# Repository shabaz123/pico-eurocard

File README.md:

# pico-eurocard

This repository contains PCB Gerber files and bill of materials for a [Pi Pico Eurocard Development Board](https://community.element14.com/products/raspberry-pi/b/blog/posts/pi-pico-eurocard-development-board). See James' [Workshop Wednesday's Video](https://community.element14.com/challenges-projects/element14-presents/workbenchwednesdays/w/documents/28083/workbench-wednesdays-70-why-you-need-a-raspberry-pi-pico-development-board-by-shabaz) which demonstrates the revision 2.0 board.

Right-click below to open in new window to watch the video for a quick explanation!

The current revision 2.2 board has a few slight impromements to make it easier to solder, and has enlarged text silkscreen as can be seen in the image below.

Latest [Schematic](https://github.com/shabaz123/pico-eurocard/blob/main/pico-euro-kicad-source/pico-euro-schematic.pdf) and [Bill of Materials](https://github.com/shabaz123/pico-eurocard/blob/main/pico-euro-kicad-source/pico-euro-rev-2-2-bill-of-materials.pdf) and [Zip file of Gerbers](https://github.com/shabaz123/pico-eurocard/blob/main/export_pico_euro_rev_2_2.zip), (click on the Download button on the right) ready for sending to any PCB factory.

License: The pico-eurocard project is distributed under the CC BY-NC-SA 4.0 license. Please share any changes you make, so that others can contribute and benefit from them.

Board Revision History

Rev 1 - Resistors R2 and R3 are mistakenly connected to GND. They should be connected to 3V3. See the rev1-i2c-fix.png file to see the fix (requires two traces to be cut, and a wire to be soldered).

Rev 1.1 - Fixes the R2 and R3 issue that Rev 1 had. Also adds connections for an SPI TFT display, and exposes I2C, GND and VSYS onto some additional pins on the edge connector for some more flexibility. Also, the 7805 regulator has a bit more space, to allow heatsinks to more easily fit.

Rev 1.2 - Adds some pads on the underside of the SOIC footprints, that are suitable for decoupling capacitors, and for optional output feedback components if the soldered SOIC component is an op-amp. Also, the corners of the board have been rounded very slightly (0.5 mm radius). Previously, the corners had no radius.

Rev 1.3 - Added some pads to make it slightly easier to plug on a daughter board made from (say) stripboard.

Rev 2.0 - Removed SPI TFT pins, since there was some incompatibility with recently available displays. Added micro SD card socket.

Rev 2.2 - Very similar to 2.0 version, but with far more legible silkscreen, and with all surface-mount components (including the micro SD socket) on one side of the board, for easier production. Also added a resistor for more gate protection with partially assembled boards.

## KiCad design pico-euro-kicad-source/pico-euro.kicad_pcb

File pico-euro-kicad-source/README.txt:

Please see the following links for more information on this project, and to comment on it:

https://community.element14.com/products/raspberry-pi/b/blog/posts/pi-pico-eurocard-development-board

https://community.element14.com/challenges-projects/element14-presents/workbenchwednesdays/w/documents/28083/workbench-wednesdays-70-why-you-need-a-raspberry-pi-pico-development-board-by-shabaz?ICID=workbenchwed-episode-list

https://community.element14.com/tags/pico_5F00_eurocard

Software Links:
https://github.com/jancumps/picoprobe/releases

https://github.com/shabaz123/rp2040tools

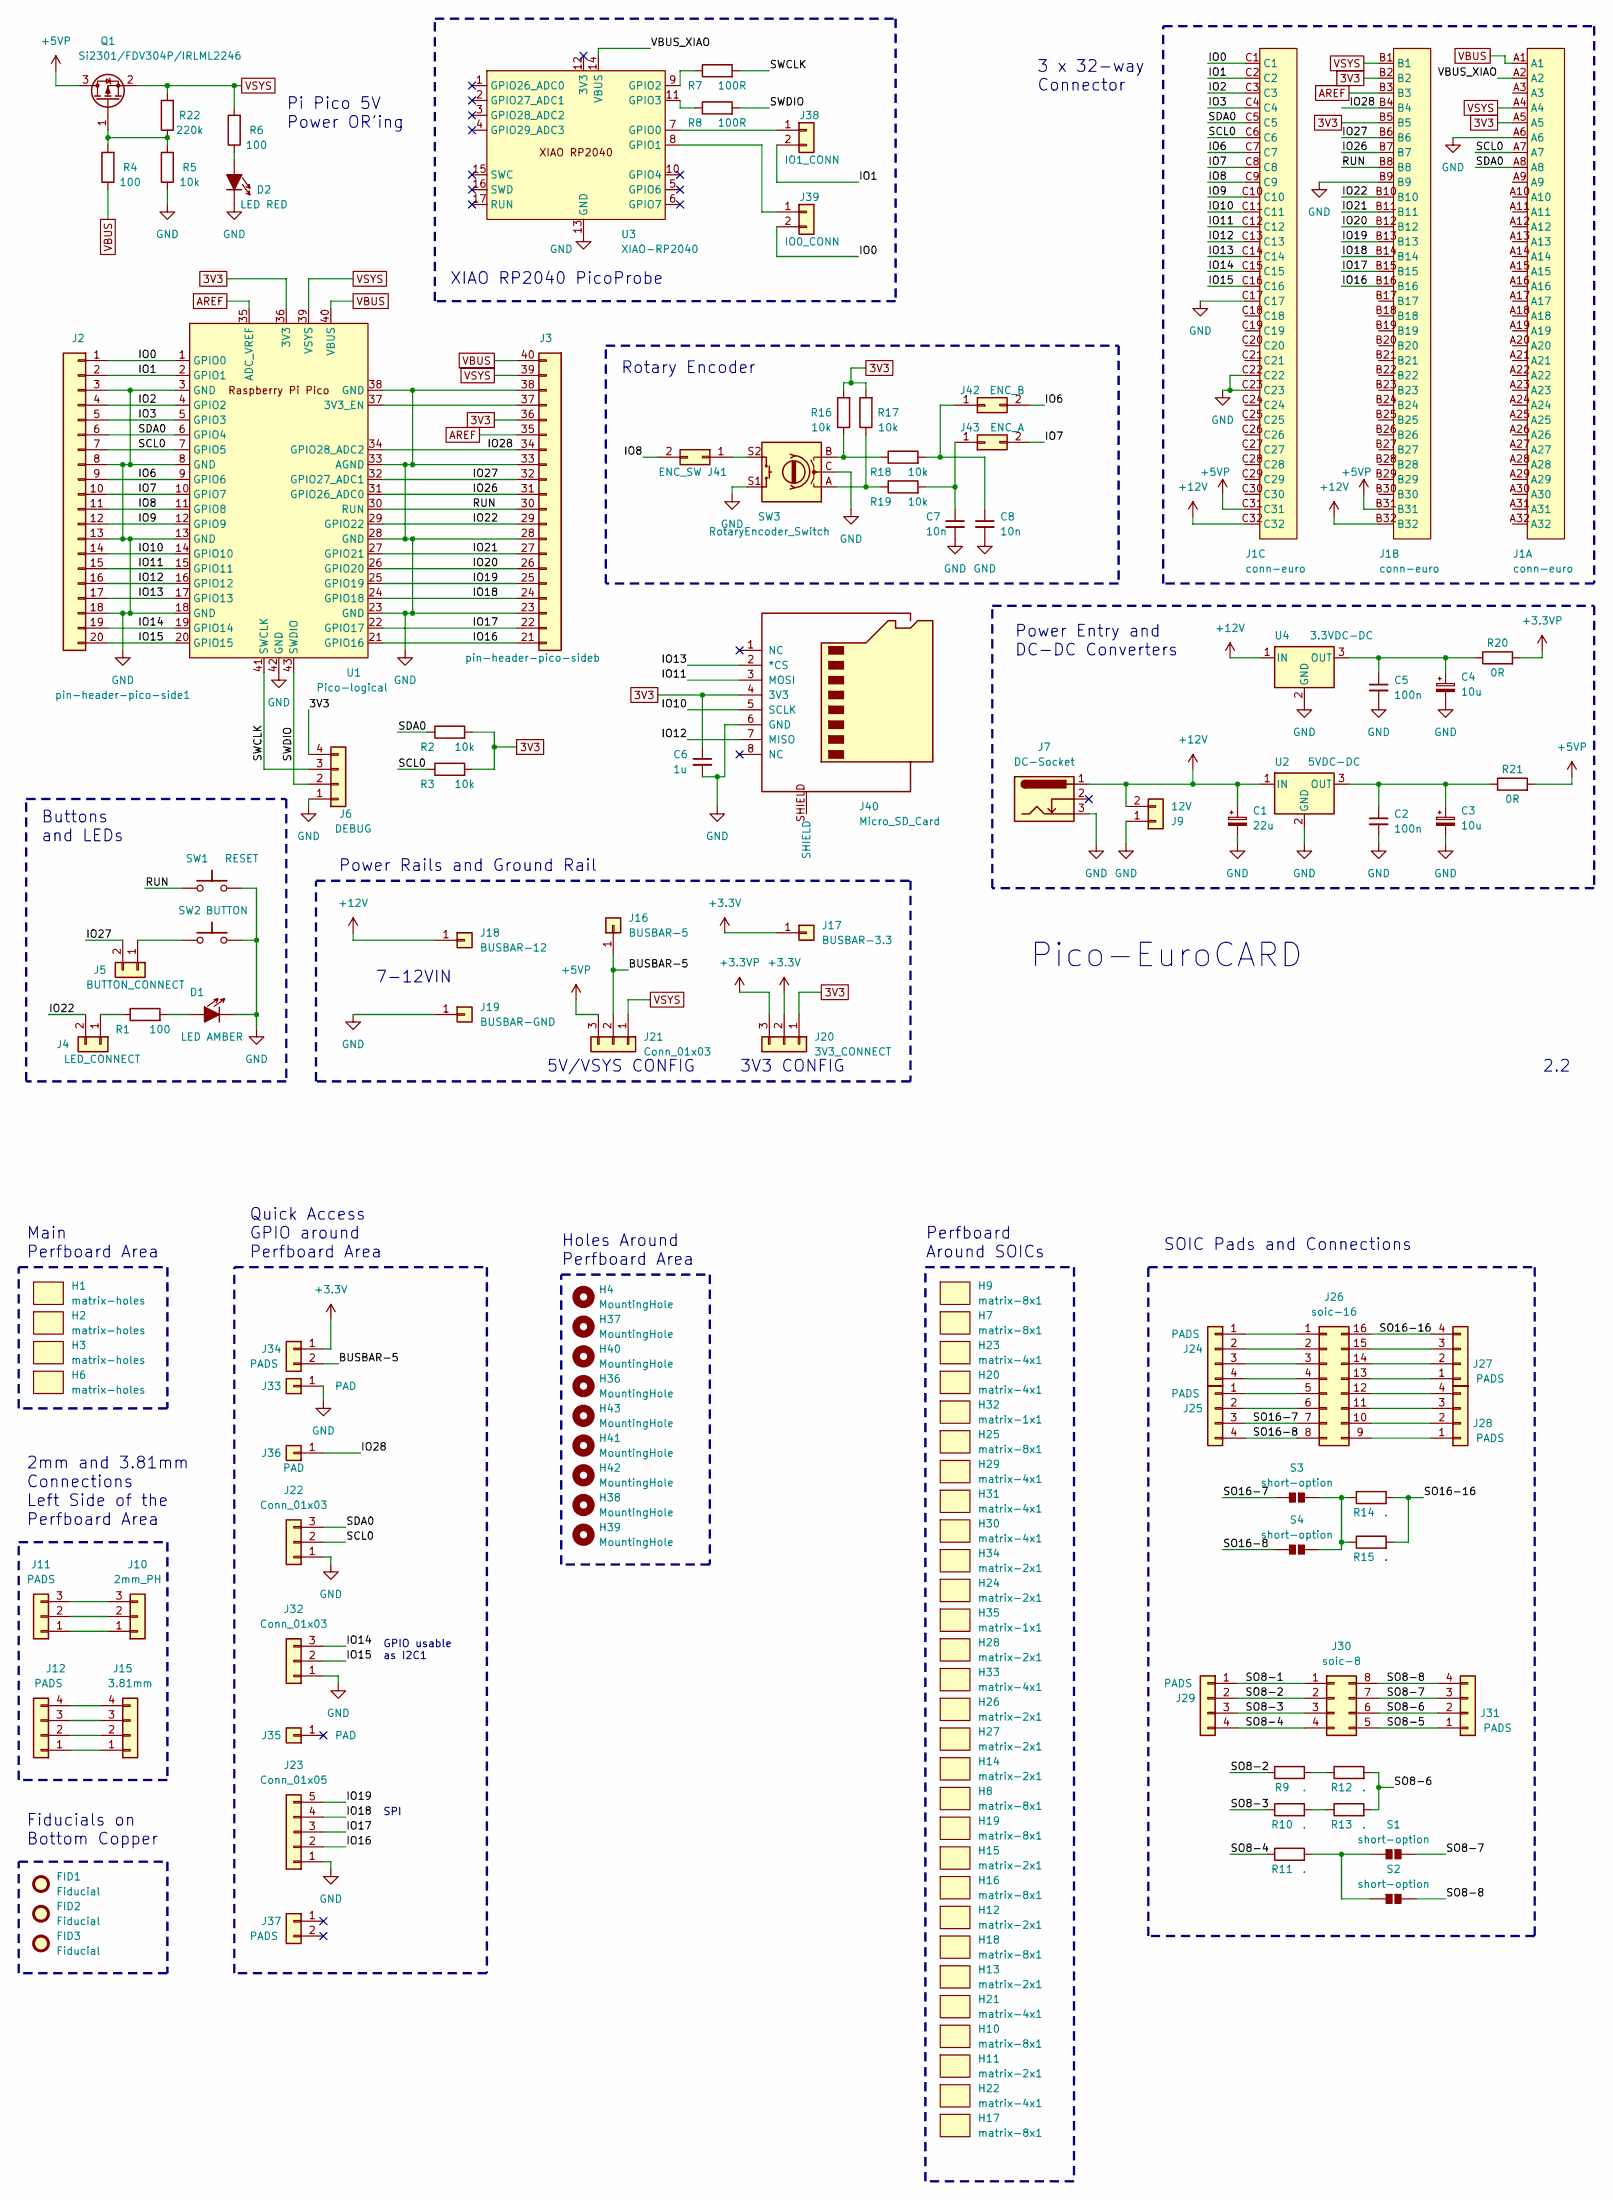
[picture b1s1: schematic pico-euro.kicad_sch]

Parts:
C1: 22u; CP_Radial_D6.3mm_P2.50mm
C2, C5: 100n; C_0805_2012Metric_Pad1.18x1.45mm_HandSolder
C3, C4: 10u; CP_Radial_D6.3mm_P2.50mm
C6: 1u; C_1210_3225Metric_Pad1.33x2.70mm_HandSolder
C7, C8: 10n; C_0805_2012Metric_Pad1.18x1.45mm_HandSolder
D1: LED AMBER; LED_D3.0mm
D2: LED RED; LED_D3.0mm
FID1, FID2, FID3: Fiducial; Fiducial_1mm_Mask2mm
H1, H2, H3, H6: matrix-holes; matrix-33-4
H4, H36, H37, H38, H39, H40, H41, H42, H43: MountingHole; HOLE_BARE_0.9mm
H7, H8, H9, H10, H16, H17, H18, H19, H25: matrix-8x1
H11, H12, H13, H14, H15, H24, H26, H27, H28, H34: matrix-2x1
H20, H21, H22, H23, H29, H30, H31, H33: matrix-4x1
H32, H35: matrix-1x1
J1: conn-euro; Eurocard-Plug-Type-C
J2: pin-header-pico-side1
J3: pin-header-pico-sideb; pin-header-pico-side2
J4: LED_CONNECT; PinHeader_1x02_P2.54mm_Vertical
J5: BUTTON_CONNECT; PinHeader_1x02_P2.54mm_Vertical
J6: DEBUG; PinHeader_1x04_P2.54mm_Vertical
J7: DC-Socket; DC-Jack-10
J9: 12V; TerminalBlock_Phoenix_PT-1,5-2-3.5-H_1x02_P3.50mm_Horizontal
J10: 2mm_PH; JST_PH_3_VERT
J11: PADS; pads3-euro
J12, J24, J25, J27, J28, J29, J31: PADS; pads4-euro
J15: 3.81mm; array-3.81
J16: BUSBAR-5; busbar-20div2
J17: BUSBAR-3.3; busbar-20
J18: BUSBAR-12; busbar-20div4
J19: BUSBAR-GND; busbar-20
J20: 3V3_CONNECT; PinHeader_1x03_P2.54mm_Vertical
J21: Conn_01x03; PinHeader_1x03_P2.54mm_Vertical
J22, J32: Conn_01x03; pads3-euro
J23: Conn_01x05; pads5-euro
J26: soic-16; SOIC-16-proto
J30: soic-8; SOIC-8-proto
J33, J35, J36: PAD; pads1-euro
J34, J37: PADS; pads2-euro
J38: IO1_CONN; PinHeader_1x02_P2.54mm_Vertical
J39: IO0_CONN; PinHeader_1x02_P2.54mm_Vertical
J40: Micro_SD_Card; microsd-generic
J41: ENC_SW; PinHeader_1x02_slim
J42: ENC_B; PinHeader_1x02_slim
J43: ENC_A; PinHeader_1x02_slim
Q1: Si2301/FDV304P/IRLML2246; SOT-23_Handsoldering
R1, R4, R6: 100; R_0805_2012Metric_Pad1.20x1.40mm_HandSolder
R2, R3, R5, R16, R17, R18, R19: 10k; R_0805_2012Metric_Pad1.20x1.40mm_HandSolder
R7, R8: 100R; R_0805_2012Metric_Pad1.20x1.40mm_HandSolder
R9, R10, R11, R12, R13, R14: .; R_0805_2012Metric_Pad1.20x1.40mm_HandSolder
R15: .; R_1210_3225Metric_Pad1.30x2.65mm_HandSolder
R20, R21: 0R; R_0805_2012Metric_Pad1.20x1.40mm_HandSolder
R22: 220k; R_0805_2012Metric_Pad1.20x1.40mm_HandSolder
S1, S2, S3, S4: short-option; short-option-small
SW1: RESET; SW_PUSH_6mm
SW2: BUTTON; SW_PUSH_6mm
SW3: RotaryEncoder_Switch; Encoder-and-Switch
U1: Pico-logical; pi-pico-euro
U2: 5VDC-DC; DCDC-78xx-replacement
U3: XIAO-RP2040
U4: 3.3VDC-DC; DCDC-78xx-replacement

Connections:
3V3: C6.1, J1.A5, J1.B2, J1.B5, J3.36, J6.4, J20.1, J40.4 (3V3), R2.2, R3.2, R16.2, R17.2, U1.36 (3V3)
+3.3VP: J20.3, R20.2
+3V3: J17.1, J20.2, J34.1
+5VP: J1.B31, J1.C31, J21.3, Q1.3 (D), R21.2
+12V: C1.1, J1.B32, J1.C32, J7.1, J9.2, J18.1, U2.1 (IN), U4.1 (IN)
/BUSBAR-5: J16.1, J21.2, J34.2
/IO0: J1.C1, J2.1, J39.2, U1.1 (GPIO0)
/IO1: J1.C2, J2.2, J38.2, U1.2 (GPIO1)
/IO2: J1.C3, J2.4, U1.4 (GPIO2)
/IO3: J1.C4, J2.5, U1.5 (GPIO3)
/IO6: J1.C7, J2.9, J42.2, U1.9 (GPIO6)
/IO7: J1.C8, J2.10, J43.2, U1.10 (GPIO7)
/IO8: J1.C9, J2.11, J41.2, U1.11 (GPIO8)
/IO9: J1.C10, J2.12, U1.12 (GPIO9)
/IO10: J1.C11, J2.14, J40.5 (SCLK), U1.14 (GPIO10)
/IO11: J1.C12, J2.15, J40.3 (MOSI), U1.15 (GPIO11)
/IO12: J1.C13, J2.16, J40.7 (MISO), U1.16 (GPIO12)
/IO13: J1.C14, J2.17, J40.2 (*CS), U1.17 (GPIO13)
/IO14: J1.C15, J2.19, J32.3, U1.19 (GPIO14)
/IO15: J1.C16, J2.20, J32.2, U1.20 (GPIO15)
/IO16: J1.B16, J3.21, J23.2, U1.21 (GPIO16)
/IO17: J1.B15, J3.22, J23.3, U1.22 (GPIO17)
/IO18: J1.B14, J3.24, J23.4, U1.24 (GPIO18)
/IO19: J1.B13, J3.25, J23.5, U1.25 (GPIO19)
/IO20: J1.B12, J3.26, U1.26 (GPIO20)
/IO21: J1.B11, J3.27, U1.27 (GPIO21)
/IO22: J1.B10, J3.29, J4.2, U1.29 (GPIO22)
/IO26: J1.B7, J3.31, U1.31 (GPIO26_ADC0)
/IO27: J1.B6, J3.32, J5.2, U1.32 (GPIO27_ADC1)
/IO28: J1.B4, J3.34, J36.1, U1.34 (GPIO28_ADC2)
/RUN: J1.B8, J3.30, SW1.1, U1.30 (RUN)
/SCL0: J1.A7, J1.C6, J2.7, J22.2, R3.1, U1.7 (GPIO5)
/SDA0: J1.A8, J1.C5, J2.6, J22.3, R2.1, U1.6 (GPIO4)
/SO8-1: J29.1, J30.1
/SO8-2: J29.2, J30.2, R9.1
/SO8-3: J29.3, J30.3, R10.1
/SO8-4: J29.4, J30.4, R11.1
/SO8-5: J30.5, J31.1
/SO8-6: J30.6, J31.2, R12.2, R13.2
/SO8-7: J30.7, J31.3, S1.2 (A)
/SO8-8: J30.8, J31.4, S2.2 (A)
/SO16-7: J25.3, J26.7, S3.1 (K)
/SO16-8: J25.4, J26.8, S4.1 (K)
/SO16-16: J26.16, J27.4, R14.2, R15.2
/SWCLK: J6.3, R7.2, U1.41 (SWCLK)
/SWDIO: J6.2, R8.2, U1.43 (SWDIO)
/VBUS_XIAO: J1.A2, U3.14 (VBUS)
AREF: J1.B3, J3.35, U1.35 (ADC_VREF)
GND: C1.2, C2.2, C3.2, C4.2, C5.2, C6.2, C7.2, C8.2, D1.1 (K), D2.1 (K), J1.A6, J1.B9, J1.C17, J1.C22, J1.C23, J2.3, J2.8, J2.13, J2.18, J3.23, J3.28, J3.33, J3.38, J6.1, J7.3, J9.1, J19.1, J22.1, J23.1, J32.1, J33.1, J40.6 (GND), R5.1, SW1.2, SW2.2, SW3.C, SW3.S1, U1.3 (GND), U1.8 (GND), U1.13 (GND), U1.18 (GND), U1.23 (GND), U1.28 (GND), U1.33 (AGND), U1.38 (GND), U1.42 (GND), U2.2 (GND), U3.13 (GND), U4.2 (GND)
unnamed: D1.2 (A), R1.2
unnamed: D2.2 (A), R6.1
unnamed: J3.37, U1.37 (3V3_EN)
unnamed: J4.1, R1.1
unnamed: J5.1, SW2.1
unnamed: J10.1, J11.1
unnamed: J10.2, J11.2
unnamed: J10.3, J11.3
unnamed: J12.1, J15.1
unnamed: J12.2, J15.2
unnamed: J12.3, J15.3
unnamed: J12.4, J15.4
unnamed: J24.1, J26.1
unnamed: J24.2, J26.2
unnamed: J24.3, J26.3
unnamed: J24.4, J26.4
unnamed: J25.1, J26.5
unnamed: J25.2, J26.6
unnamed: J26.9, J28.1
unnamed: J26.10, J28.2
unnamed: J26.11, J28.3
unnamed: J26.12, J28.4
unnamed: J26.13, J27.1
unnamed: J26.14, J27.2
unnamed: J26.15, J27.3
unnamed: J38.1, U3.7 (GPIO0)
unnamed: J39.1, U3.8 (GPIO1)
unnamed: J41.1, SW3.S2
unnamed: C8.1, J42.1, R18.2
unnamed: C7.1, J43.1, R19.2
unnamed: Q1.1 (G), R4.2, R5.2, R22.1
unnamed: R10.2, R13.1
unnamed: R9.2, R12.1
unnamed: R16.1, R18.1, SW3.B
unnamed: R17.1, R19.1, SW3.A
unnamed: R11.2, S1.1 (K), S2.1 (K)
unnamed: R14.1, R15.1, S3.2 (A), S4.2 (A)
unnamed: C2.1, C3.1, R21.1, U2.3 (OUT)
unnamed: R7.1, U3.9 (GPIO2)
unnamed: R8.1, U3.11 (GPIO3)
unnamed: C4.1, C5.1, R20.1, U4.3 (OUT)
VBUS: J1.A1, J3.40, R4.1, U1.40 (VBUS)
VSYS: J1.A4, J1.B1, J3.39, J21.1, Q1.2 (S), R6.2, R22.2, U1.39 (VSYS)

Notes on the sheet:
3V3 CONFIG
Quick Access GPIO around Perfboard Area
5V/VSYS CONFIG
Buttons and LEDs
Rotary Encoder
Holes Around Perfboard Area
7-12VIN
Pi Pico 5V Power OR'ing
Perfboard Around SOICs
Power Entry and DC-DC Converters
Pico-EuroCARD
Power Rails and Ground Rail
XIAO RP2040 PicoProbe
Main Perfboard Area
Fiducials on Bottom Copper
2mm and 3.81mm Connections Left Side of the Perfboard Area
3 x 32-way Connector
GPIO usable as I2C1
SOIC Pads and Connections
2.2
SPI

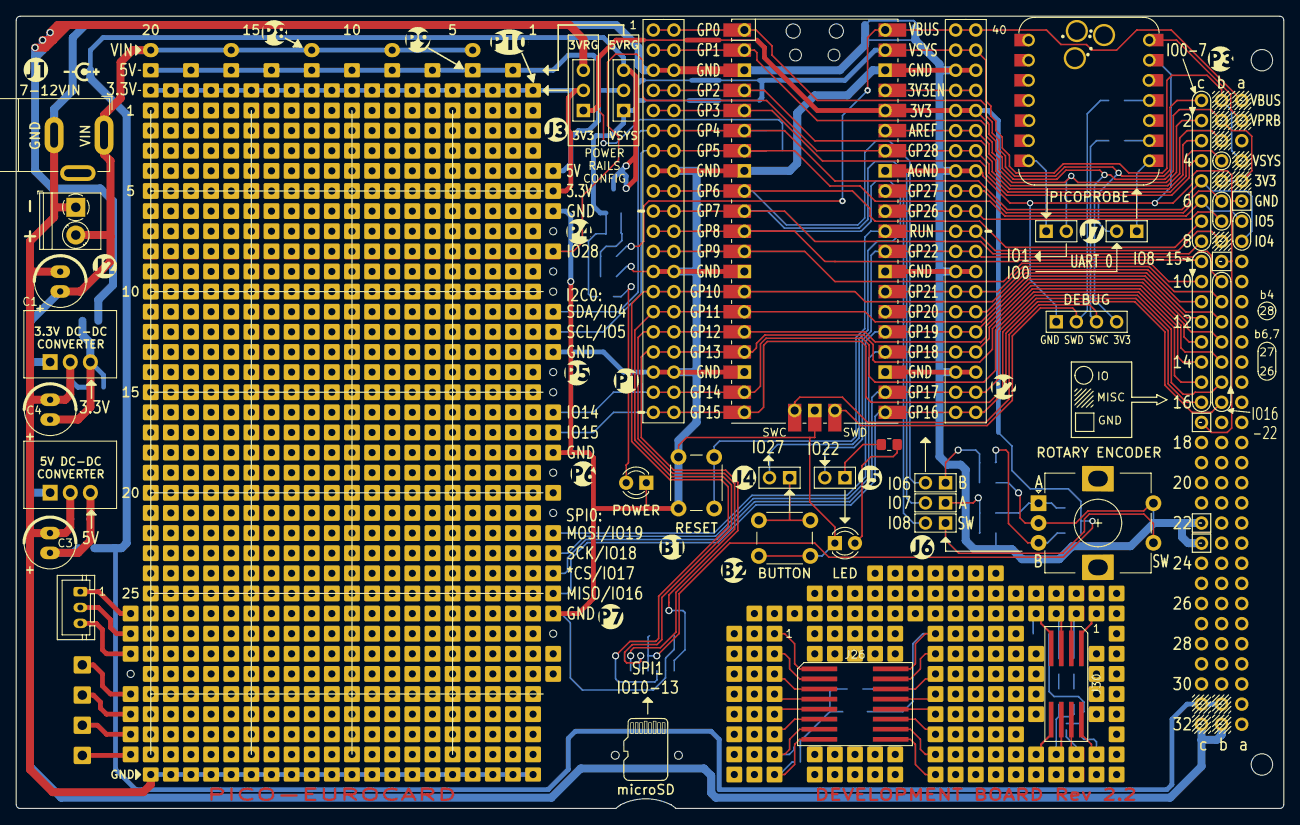
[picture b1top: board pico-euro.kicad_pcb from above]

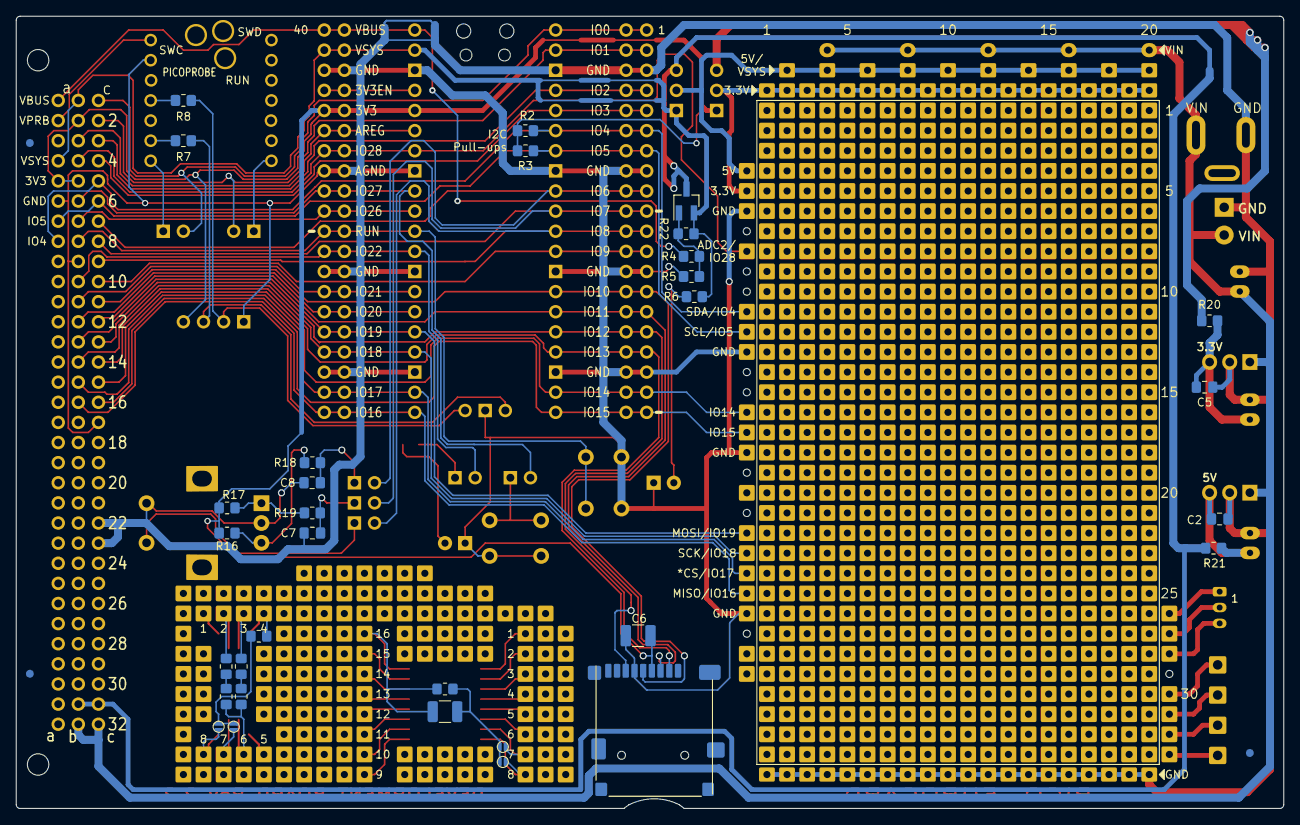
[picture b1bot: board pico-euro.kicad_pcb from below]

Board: 2 copper layers, 160.0 x 100.0 mm, 129 parts (68 on the bottom side), 92 nets.
